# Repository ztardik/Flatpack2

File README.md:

# Flatpack2
Eltek Flatpack 2 connector

Early beta - NOT tested yet!

Use 2oz copper if possible.

Current capacity (calculated):

1oz - 17A @ Temperature Rise 20°C

2oz - 28A @ Temperature Rise 20°C

1oz - 23A @ Temperature Rise 40°C

2oz - 38A @ Temperature Rise 40°C

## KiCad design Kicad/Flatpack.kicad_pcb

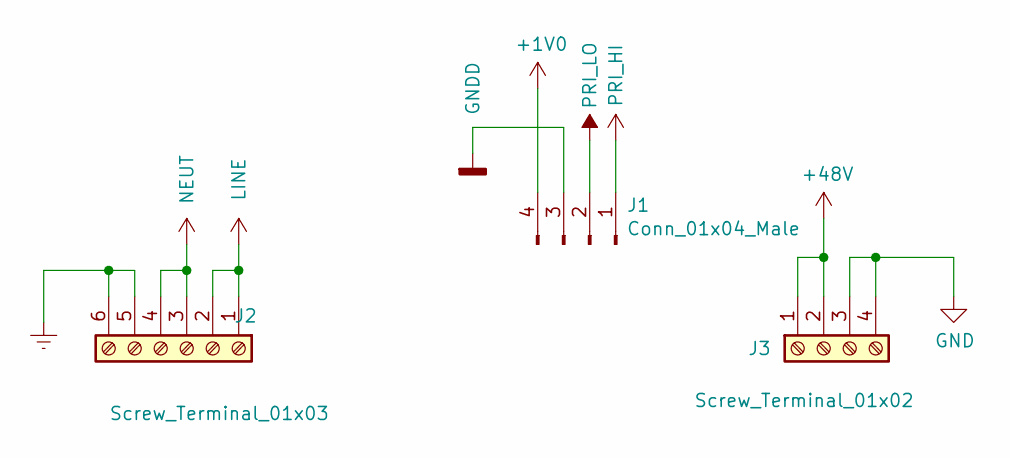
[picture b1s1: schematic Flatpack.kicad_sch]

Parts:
J1: Conn_01x04_Male; JST_EH_B4B-EH-A_1x04_P2.50mm_Vertical
J2: Screw_Terminal_01x03; TerminalBlock_Phoenix_MKDS-3-6-5.08_1x06_P5.08mm_Horizontal
J3: Screw_Terminal_01x02; TerminalBlock_Phoenix_MKDS-3-4-5.08_1x04_P5.08mm_Horizontal

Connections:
+1V0: J1.4
+48V: J3.1, J3.2
Earth: J2.5, J2.6
GND: J3.3, J3.4
GNDD: J1.3
LINE: J2.1, J2.2
NEUT: J2.3, J2.4
PRI_HI: J1.1
PRI_LO: J1.2

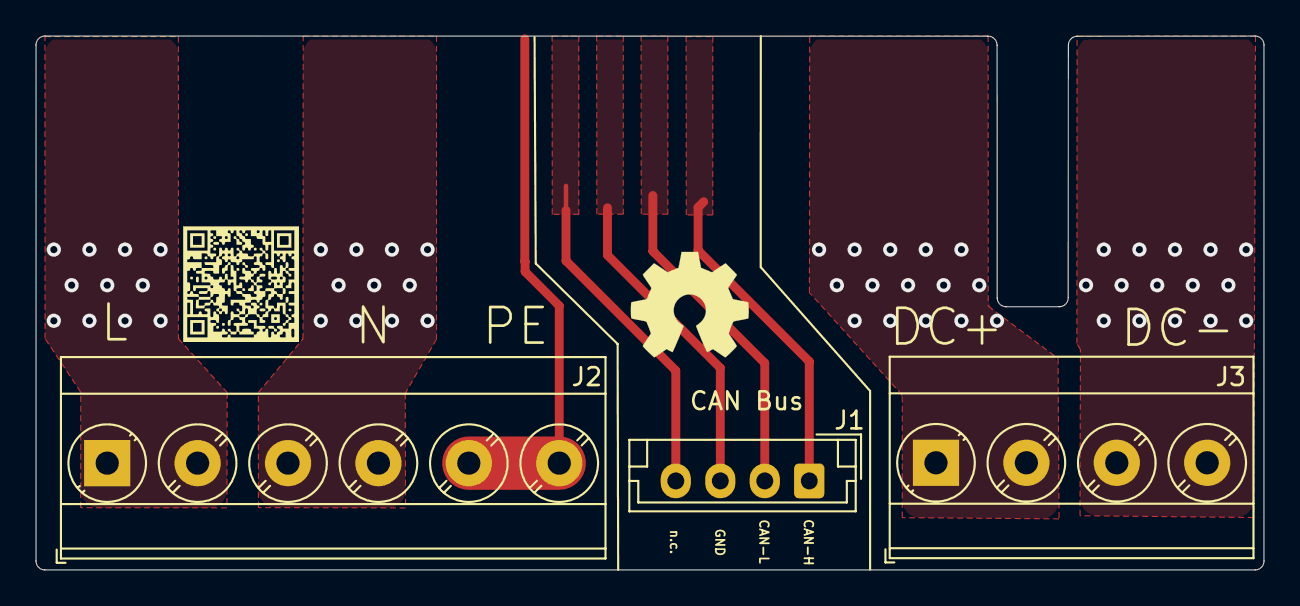
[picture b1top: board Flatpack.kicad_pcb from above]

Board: 2 copper layers, 69.0 x 30.0 mm, 3 parts (0 on the bottom side), 5 nets.

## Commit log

2020-05-18 Initial upload
2020-05-19 Added images...
2020-05-19 Add current rating
